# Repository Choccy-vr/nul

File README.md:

# nul
A WLED controller that blends into the background

## Description
Nul is a small, compact WLED controller that is meant to go in line with your LED strip. Powered by an ESP32 C3 in a super small 11x40mm package.

## Instructions 
1. Plug the board into your computer and update WLED if you need to (preinstalled with v16.0.1)
2. Connect your LED Strip to your board
3. Attach your antenna
4. Plug in any USB PD Power source and enjoy
5. Connect to the WLED-AP Access point and connect it to the internet.

## BOM
|Product Name|Product Description|Product Link       |Product Cost|Total |
|------------|-------------------|-------------------|------------|------|
|PCB         |PCB + PCBA         |https://jlcpcb.com/|$47.22      |$54.60|

## Pictures

### Schematic

### PCB

### Built

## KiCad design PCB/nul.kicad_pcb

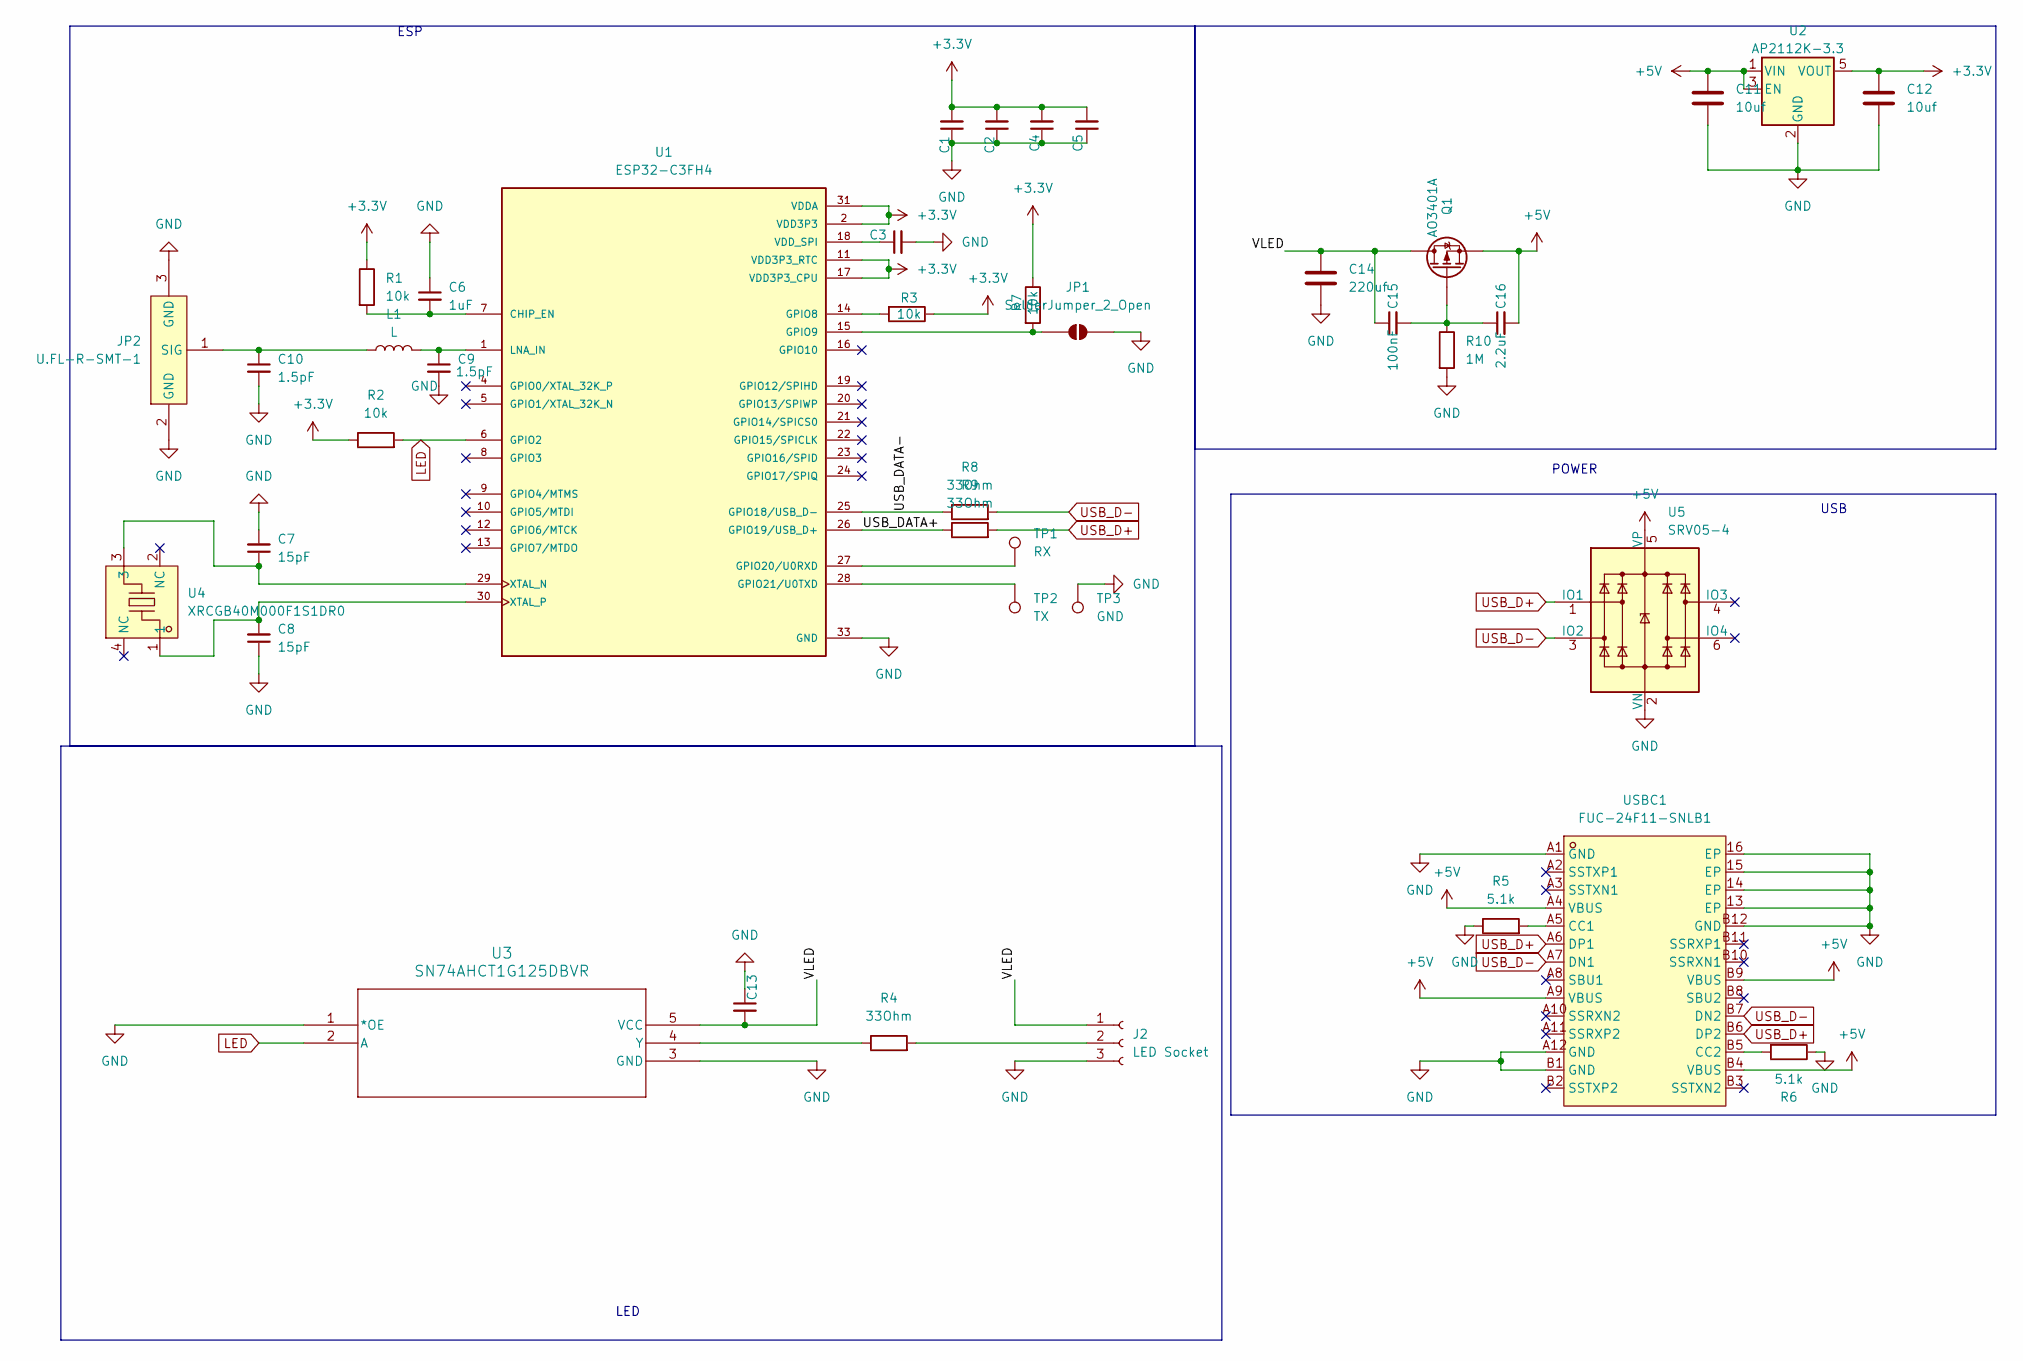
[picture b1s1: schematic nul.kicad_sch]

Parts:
C1, C2, C4, C5, C13: 0.1uF ceramic; C_0402_1005Metric; LCSC Part C1525
C3, C6: 1uF; C_0402_1005Metric; LCSC Part C52923
C7, C8: 15pF; C_0402_1005Metric; LCSC Part C1548
C9, C10: 1.5pF; C_0402_1005Metric; LCSC Part C1552
C11: 10uf; C_0402_1005Metric
C12: 10uf; C_0402_1005Metric; LCSC Part C15525
C14: 220uf; C_1210_3225Metric; LCSC Part C400951
C15: 100nF; C_0402_1005Metric; LCSC Part C1525
C16: 2.2uF; C_0402_1005Metric; LCSC Part C12530
J2: LED Socket; PinHeader_1x03_P2.54mm_Vertical
JP1: SolderJumper_2_Open; SolderJumper-2_P1.3mm_Open_RoundedPad1.0x1.5mm
JP2: U.FL-R-SMT-1; RF-SMD_FRF05002-JSS103M; MPN U.FL-R-SMT-1(80); LCSC Part C88374
L1: L; L_0402_1005Metric; LCSC Part C27122
Q1: AO3401A; SOT-23; LCSC Part C15127
R1, R2, R3, R7: 10k; R_0402_1005Metric; LCSC Part C25744
R4, R8, R9: 33Ohm; R_0402_1005Metric; LCSC Part C25105
R5, R6: 5.1k; R_0402_1005Metric; LCSC Part C25905
R10: 1M; R_0402_1005Metric; LCSC Part C26083
TP1: RX; TestPoint_Pad_D1.5mm
TP2: TX; TestPoint_Pad_D1.5mm
TP3: GND; TestPoint_Pad_D1.5mm
U1: ESP32-C3FH4; QFN50P500X500X90-33N; PARTREV 2.0; LCSC Part C2858491
U2: AP2112K-3.3; SOT-23-5; LCSC Part C22365427
U3: SN74AHCT1G125DBVR; DBV5; LCSC Part C7484
U4: XRCGB40M000F1S1DR0; CRYSTAL-SMD_4P-L2.0-W1.6-BL; MPN XRCGB40M000F1S1DR0; LCSC Part C1870453
U5: SRV05-4; SOT-23-6; LCSC Part C7420376
USBC1: FUC-24F11-SNLB1; USB-C-SMD_C67380; MPN 918-418K2023C40002; LCSC Part C67380

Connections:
+3.3V: C1.2, C2.2, C4.2, C5.2, C12.1, R1.1, R2.1, R3.1, R7.1, U1.2 (VDD3P3), U1.3 (VDD3P3), U1.11 (VDD3P3_RTC), U1.17 (VDD3P3_CPU), U1.31 (VDDA), U1.32 (VDDA), U2.5 (VOUT)
+5V: C11.1, C16.2, Q1.2 (S), U2.1 (VIN), U2.3 (EN), U5.5 (VP), USBC1.A4 (VBUS), USBC1.A9 (VBUS), USBC1.B4 (VBUS), USBC1.B9 (VBUS)
/USB_DATA+: R9.1, U1.26 (GPIO19/USB_D+)
/USB_DATA-: R8.1, U1.25 (GPIO18/USB_D-)
/VLED: C13.2, C14.1, C15.1, J2.1, Q1.3 (D), U3.5 (VCC)
GND: C1.1, C2.1, C3.2, C4.1, C5.1, C6.1, C7.2, C8.1, C9.2, C10.2, C11.2, C12.2, C13.1, C14.2, J2.3, JP1.2 (B), JP2.2 (GND), JP2.3 (GND), R5.1, R6.1, R10.2, TP3.1, U1.33 (GND), U2.2 (GND), U3.1 (*OE), U3.3 (GND), U5.2 (VN), USBC1.13 (EP), USBC1.14 (EP), USBC1.15 (EP), USBC1.16 (EP), USBC1.A1 (GND), USBC1.A12 (GND), USBC1.B1 (GND), USBC1.B12 (GND)
LED: R2.2, U1.6 (GPIO2), U3.2 (A)
unnamed: J2.2, R4.2
unnamed: JP1.1 (A), R7.2, U1.15 (GPIO9)
unnamed: C10.1, JP2.1 (SIG), L1.1
unnamed: C15.2, C16.1, Q1.1 (G), R10.1
unnamed: C6.2, R1.2, U1.7 (CHIP_EN)
unnamed: R3.2, U1.14 (GPIO8)
unnamed: TP1.1, U1.27 (GPIO20/U0RXD)
unnamed: TP2.1, U1.28 (GPIO21/U0TXD)
unnamed: C9.1, L1.2, U1.1 (LNA_IN)
unnamed: C3.1, U1.18 (VDD_SPI)
unnamed: C7.1, U1.29 (XTAL_N), U4.3
unnamed: C8.2, U1.30 (XTAL_P), U4.1
unnamed: R4.1, U3.4 (Y)
unnamed: R5.2, USBC1.A5 (CC1)
unnamed: R6.2, USBC1.B5 (CC2)
USB_D+: R9.2, U5.1 (IO1), USBC1.A6 (DP1), USBC1.B6 (DP2)
USB_D-: R8.2, U5.3 (IO2), USBC1.A7 (DN1), USBC1.B7 (DN2)

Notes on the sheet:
ESP
POWER
LED
USB

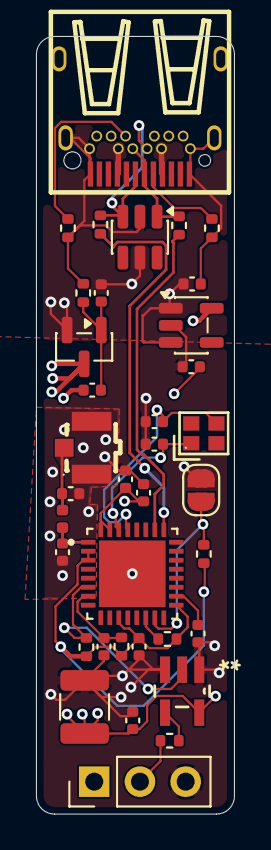
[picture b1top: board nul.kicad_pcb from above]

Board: 4 copper layers, 11.0 x 43.2 mm, 36 parts (0 on the bottom side), 22 nets.

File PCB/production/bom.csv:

Designator,Footprint,Quantity,Value,LCSC Part #
"C10, C9",0402,2,1.5pF,C1552
C11,0402,1,10uf,
C12,0402,1,10uf,C15525
"C13, C2, C4, C5",0402,4,0.1uF ceramic,C1525
C14,1210,1,220uf,C400951
C15,0402,1,100nF,C1525
C16,0402,1,2.2uF,C12530
"C3, C6",0402,2,1uF,C52923
"C7, C8",0402,2,15pF,C1548
J2,PinHeader_1x03_P2.54mm_Vertical,1,LED Socket,
JP2,RF-SMD_FRF05002-JSS103M,1,U.FL-R-SMT-1,C88374
L1,0402,1,L,C27122
Q1,SOT-23,1,AO3401A,C15127
"R1, R2, R3, R7",0402,4,10k,C25744
R10,0402,1,1M,C26083
"R4, R8, R9",0402,3,33Ohm,C25105
"R5, R6",0402,2,5.1k,C25905
U1,QFN50P500X500X90-33N,1,ESP32-C3FH4,C2858491
U2,SOT-23-5,1,AP2112K-3.3,C22365427
U3,DBV5,1,SN74AHCT1G125DBVR,C7484
U4,CRYSTAL-SMD_4P-L2.0-W1.6-BL,1,XRCGB40M000F1S1DR0,C1870453
U5,SOT-23-6,1,SRV05-4,C7420376
USBC1,USB-C-SMD_C67380,1,FUC-24F11-SNLB1,C67380
